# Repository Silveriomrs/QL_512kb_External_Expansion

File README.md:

# SINCLAIR QL 512kB External Rom Expansion

**This board will provide up to 512kB aditional of static RAM (*fast-ram*) to the sinclair QL.**

> [!NOTE]
> **Last update: 14-10-2026 PCB revision 1.1 in testing phase.**
> 
> Use revision 1.0 for stable version till 1.1 testing is finished.

## Introduction & Purpose

The projects merges from the need of a expansion board OpenHardware & OpenSource that could adds aditional RAM memory to a stock QL. It is widely covered by other similar projects like the one that was taking as base of this one.

Regardless there are some needs not covered and that this project aim to solve (*what have been achived*). The most important is that other projects can be combinend by advance users with electronic skills due to soldering requirements but not for final users. Also other solutions make difficult to use in/and with other hardware developments (*every address conflict may result in the must of rewiring and modifying boards to change address*).

So once got the need, there was a OpenHardware project that was a very good point to start and saved a lot of time. This project is also based in the works from other people who gives a lot of time and effort to the community. All of them are  [referenced on the credits](#Credits-&-License).

Finally, with the same spirit to give to the users another device to the community for free use, also something that would not be lost if the author cannot produce them (what is normal in a retro-tech area). Everyone could make their own board or to adquire from friends or sellers. 

**The only restrictions: the credits have to remain in the PCB and derivate projects.**

## Advantages of the memory expansion

For developments also it gives a special feature not pressent in other developments, it is that developers could play around with switches without need to solder and test them directly with their own hardware projects. Saving time and reducing the risk of damage for soldering, and continuos inserting/removing card actions.

Thanks to the use of switches it doesn't need any soldering skill at all. So final users can change it in combination with later devices (when it is possible) in an easy way. Just changing switchs setup.

Moreover also for electrical reasons the ground plane was increased, and in order to make easier the soldering process and repairing part of the components have change orientation an places.

Passtrough connector now go directly since they are not differential/balanced signals to extremes of the board. What means a reduction of the induction side effects. It also implies that the distances are shorter for signals what may result in more compatibilities attributes.

On the board you have extra information that is helpful for final users but also for developers.

Full documentation and wiki page under construction

---

---

---
**Boards work fine in the QL used for testing**

Two board can be stacked to got a maximun of 898Kb of Memory (*same as Miracle's Trump Card*).

> [!CAUTION]
> Be aware **you can not have 2 memory expansion in same area** (*Jose Leandro's QBide, Trump Card, etc*).

Provide a expansion conector to allow conect aditional interfaces.

There area available 4 configuration trough switches in the PCB.
* 00 => 512kB - This is the standar 512kB expansion for any QL
* 01 => 256kB - This is for use as a second expansion, use the full QL space for a maximun of 898kB, be aware that this is incompatible with a lot of expansion card, so use with caution (Any expansion card that do not use jumper/switch for configuration will be incompatible).
* 10 => 192kB - Similar to 256kB provide aditional space for expansion cards correctly configured.
* 11 => 128kB - Similar to 256kB provide aditional space for expansion cards correctly configured.

> [!IMPORTANT]
> Be aware that **the configuration of 128Kb can not be installed alone**.

For be able to use 128kB, for a total of 768kB, is mandatory to have an aditional expansion card that put ROM in address E00000h, in other case the QL ROM will hang indicating RAM malfunction, because a weired overlap of the internal 128kB with this external 128kB.

---

# Gerber file

Gerbers ready to use. Labels are ready for ordering PCBs with JLCPCB but you can use your favourite maker or built it by yourself.

[Click here to download the Gerber](Gerber/Gerber_Popopo_QL_RAM_Expansion_v1a.zip) 

---

In the GAL folder there is the source code to be compiled with GALasm that you can found here: https://github.com/daveho/GALasm

## Mini Trump Card Compatibility

Alvaro Alea has done a version of the trump card disk interface here: https://github.com/alvaroalea/QL_MiniTrump3 , this interface do not provide memory like the original one. You can combine two of this card and the minitrump to got the same of the original trump card.

> [!IMPORTANT] 
> You should conect the 512Kb Card to the QL, the MiniTrump Card to the 512Kb, and the +256Kb card to the Mini Trump, and in this board you need to change Switch (*SW1*) to 2-3 to allow the Minitrump card to coordinate with the second memory card.

## Combination with other cards
With other expansion card you could reach extra RAM. Next pictures shows the results.

> [!IMPORTANT]
> For it, it requires to set the switchs properly and be in the right place in the chain of expansion cards. *Some setting in other boards may be needed*.

## Precautions

Some precautions must be taken in order to prevent accidental damage in the system. The next are the most common and important recomendations.

* Do not connect it with the QL powered. Disconnect the QL Power cable before to connect it.
* Do not change the switchs position with the QL powered.
* Do not connect to a damaged QL, it may destroy de Ram Expansion board.
* Recomendation. before to combine with another expansion card, be sure they not share same address.
* Recomendation. Be aware about static danger that may result in damage of the board. Take precautions if needed.

# Disclamer
Use it under your own risk. I take not responsability for any damage in your system.
Read the information to avoid any accidental damage.

# Credits & License
Original project of (C) 2022 Alvaro Alea Fernandez, who based his development on the work of McLeod Ideafix, Jose Leandro, Zerover and tcat among others. 

Thanks to Alberto Benítez (Lince) for his support in improvements the signals.

License under: CERN Open Hardware Licence Version 2 - Strongly Reciprocal

https://ohwr.org/cern_ohl_s_v2.txt

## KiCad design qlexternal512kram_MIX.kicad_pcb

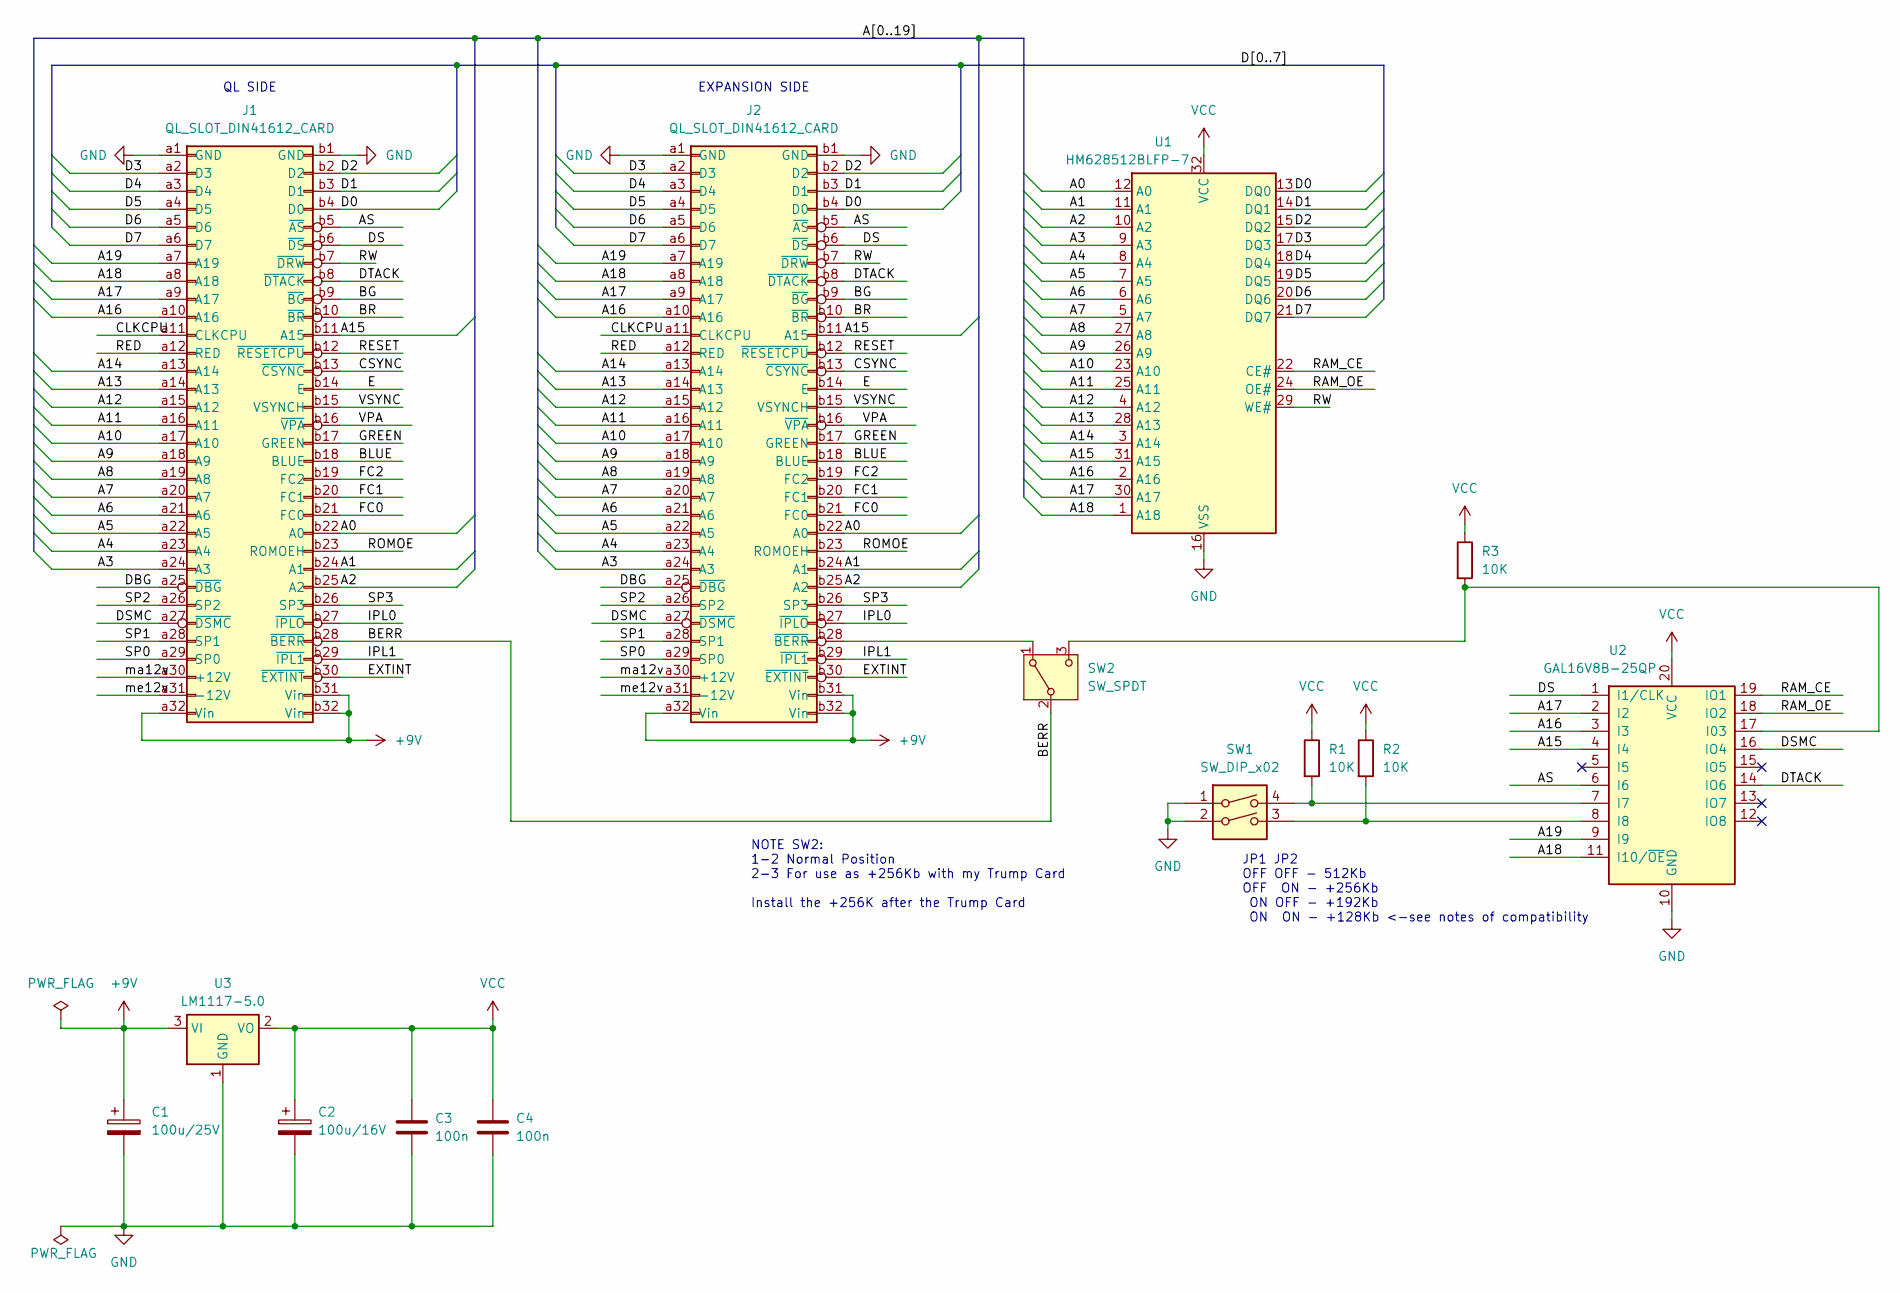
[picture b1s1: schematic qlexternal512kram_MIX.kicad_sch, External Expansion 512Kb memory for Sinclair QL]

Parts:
C1: 100u/25V; CP_Elec_6.3x5.4
C2: 100u/16V; CP_Elec_6.3x5.4
C3, C4: 100n; C_1206_3216Metric_Pad1.33x1.80mm_HandSolder
J1: QL_SLOT_DIN41612_CARD; DIN41612_B_2x32_Female_Horizontal_THT
J2: QL_SLOT_DIN41612_CARD; DIN41612_B_2x32_Male_Horizontal_THT
R1, R2, R3: 10K; R_1206_3216Metric_Pad1.30x1.75mm_HandSolder
SW1: SW_DIP_x02; SW_DIP_SPSTx02_Slide_KingTek_DSHP02TS_W7.62mm_P1.27mm
SW2: SW_SPDT; SW_SPDT_PCM12
U1: HM628512BLFP-7; SOP-32_11.305x20.495mm_P1.27mm
U2: GAL16V8B-25QP; DIP-20_W7.62mm_LongPads
U3: LM1117-5.0; SOT-223-3_TabPin2

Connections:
+9V: C1.1, J1.a32 (Vin), J1.b31 (Vin), J1.b32 (Vin), J2.a32 (Vin), J2.b31 (Vin), J2.b32 (Vin), U3.3 (VI)
/A0: J1.b22 (A0), J2.b22 (A0), U1.12 (A0)
/A1: J1.b24 (A1), J2.b24 (A1), U1.11 (A1)
/A2: J1.b25 (A2), J2.b25 (A2), U1.10 (A2)
/A3: J1.a24 (A3), J2.a24 (A3), U1.9 (A3)
/A4: J1.a23 (A4), J2.a23 (A4), U1.8 (A4)
/A5: J1.a22 (A5), J2.a22 (A5), U1.7 (A5)
/A6: J1.a21 (A6), J2.a21 (A6), U1.6 (A6)
/A7: J1.a20 (A7), J2.a20 (A7), U1.5 (A7)
/A8: J1.a19 (A8), J2.a19 (A8), U1.27 (A8)
/A9: J1.a18 (A9), J2.a18 (A9), U1.26 (A9)
/A10: J1.a17 (A10), J2.a17 (A10), U1.23 (A10)
/A11: J1.a16 (A11), J2.a16 (A11), U1.25 (A11)
/A12: J1.a15 (A12), J2.a15 (A12), U1.4 (A12)
/A13: J1.a14 (A13), J2.a14 (A13), U1.28 (A13)
/A14: J1.a13 (A14), J2.a13 (A14), U1.3 (A14)
/A15: J1.b11 (A15), J2.b11 (A15), U1.31 (A15), U2.4 (I4)
/A16: J1.a10 (A16), J2.a10 (A16), U1.2 (A16), U2.3 (I3)
/A17: J1.a9 (A17), J2.a9 (A17), U1.30 (A17), U2.2 (I2)
/A18: J1.a8 (A18), J2.a8 (A18), U1.1 (A18), U2.11 (I10/~OE)
/A19: J1.a7 (A19), J2.a7 (A19), U2.9 (I9)
/AS: J1.b5 (~AS), J2.b5 (~AS), U2.6 (I6)
/BERR: J1.b28 (~BERR), SW2.2 (B)
/BG: J1.b9 (~BG), J2.b9 (~BG)
/BLUE: J1.b18 (BLUE), J2.b18 (BLUE)
/BR: J1.b10 (~BR), J2.b10 (~BR)
/CLKCPU: J1.a11 (CLKCPU), J2.a11 (CLKCPU)
/CSYNC: J1.b13 (~CSYNC), J2.b13 (~CSYNC)
/D0: J1.b4 (D0), J2.b4 (D0), U1.13 (DQ0)
/D1: J1.b3 (D1), J2.b3 (D1), U1.14 (DQ1)
/D2: J1.b2 (D2), J2.b2 (D2), U1.15 (DQ2)
/D3: J1.a2 (D3), J2.a2 (D3), U1.17 (DQ3)
/D4: J1.a3 (D4), J2.a3 (D4), U1.18 (DQ4)
/D5: J1.a4 (D5), J2.a4 (D5), U1.19 (DQ5)
/D6: J1.a5 (D6), J2.a5 (D6), U1.20 (DQ6)
/D7: J1.a6 (D7), J2.a6 (D7), U1.21 (DQ7)
/DBG: J1.a25 (~DBG), J2.a25 (~DBG)
/DS: J1.b6 (~DS), J2.b6 (~DS), U2.1 (I1/CLK)
/DSMC: J1.a27 (~DSMC), J2.a27 (~DSMC), U2.16 (IO4)
/DTACK: J1.b8 (~DTACK), J2.b8 (~DTACK), U2.14 (IO6)
/E: J1.b14 (E), J2.b14 (E)
/EXTINT: J1.b30 (~EXTINT), J2.b30 (~EXTINT)
/FC0: J1.b21 (FC0), J2.b21 (FC0)
/FC1: J1.b20 (FC1), J2.b20 (FC1)
/FC2: J1.b19 (FC2), J2.b19 (FC2)
/GREEN: J1.b17 (GREEN), J2.b17 (GREEN)
/IPL0: J1.b27 (~IPLO), J2.b27 (~IPLO)
/IPL1: J1.b29 (~IPL1), J2.b29 (~IPL1)
/RAM_CE: U1.22 (CE#), U2.19 (IO1)
/RAM_OE: U1.24 (OE#), U2.18 (IO2)
/RED: J1.a12 (RED), J2.a12 (RED)
/RESET: J1.b12 (~RESETCPU), J2.b12 (~RESETCPU)
/ROMOE: J1.b23 (ROMOEH), J2.b23 (ROMOEH)
/RW: J1.b7 (~DRW), J2.b7 (~DRW), U1.29 (WE#)
/SP0: J1.a29 (SP0), J2.a29 (SP0)
/SP1: J1.a28 (SP1), J2.a28 (SP1)
/SP2: J1.a26 (SP2), J2.a26 (SP2)
/SP3: J1.b26 (SP3), J2.b26 (SP3)
/VPA: J1.b16 (~VPA), J2.b16 (~VPA)
/VSYNC: J1.b15 (VSYNCH), J2.b15 (VSYNCH)
/ma12v: J1.a30 (+12V), J2.a30 (+12V)
/me12v: J1.a31 (-12V), J2.a31 (-12V)
GND: C1.2, C2.2, C3.2, C4.2, J1.a1 (GND), J1.b1 (GND), J2.a1 (GND), J2.b1 (GND), SW1.1, SW1.2, U1.16 (VSS), U2.10 (GND), U3.1 (GND)
unnamed: J2.b28 (~BERR), SW2.1 (A)
unnamed: R3.2, SW2.3 (C), U2.17 (I03)
unnamed: R1.2, SW1.4, U2.7 (I7)
unnamed: R2.2, SW1.3, U2.8 (I8)
VCC: C2.1, C3.1, C4.1, R1.1, R2.1, R3.1, U1.32 (VCC), U2.20 (VCC), U3.2 (VO)

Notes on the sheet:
NOTE SW2: 1-2 Normal Position 2-3 For use as +256Kb with my Trump Card Install the +256K after the Trump Card
EXPANSION SIDE
JP1 JP2 OFF OFF - 512Kb OFF ON - +256Kb ON OFF - +192Kb ON ON - +128Kb <-see notes of compatibility
QL SIDE

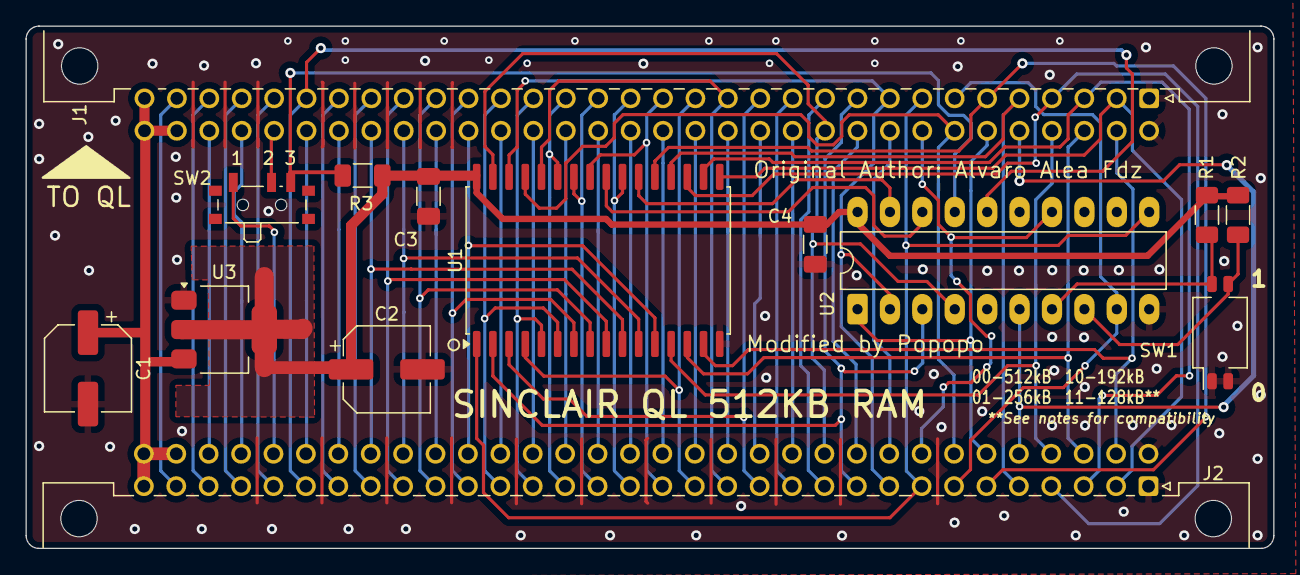
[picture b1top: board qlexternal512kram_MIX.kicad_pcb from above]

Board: 2 copper layers, 97.8 x 40.9 mm, 15 parts (1 on the bottom side), 68 nets.

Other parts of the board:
QR*****: QR_RAM_CODE

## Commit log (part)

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2024-11-21 modifying it
2024-11-22 Changing PCB size and components orientation
2024-11-27 version pre-release 1
2024-11-28 added labels
2024-11-30 produced Gerber vers 1a
2024-12-02 updating schema and symbols
2024-12-15 updating project info
2024-12-15 updating project info 2

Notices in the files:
qlexternal512kram_MIX.kicad_pcb:
(C) 2022 Alvaro Alea Fdz.
Under License
Licensed under Cern OHL-S
